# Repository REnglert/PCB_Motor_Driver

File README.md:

# PCB_Motor_Driver

This my designed, printed, soldered, and tested 12V motor driver. 

## Schematic 

## PCB Layout 

## Soldered Board

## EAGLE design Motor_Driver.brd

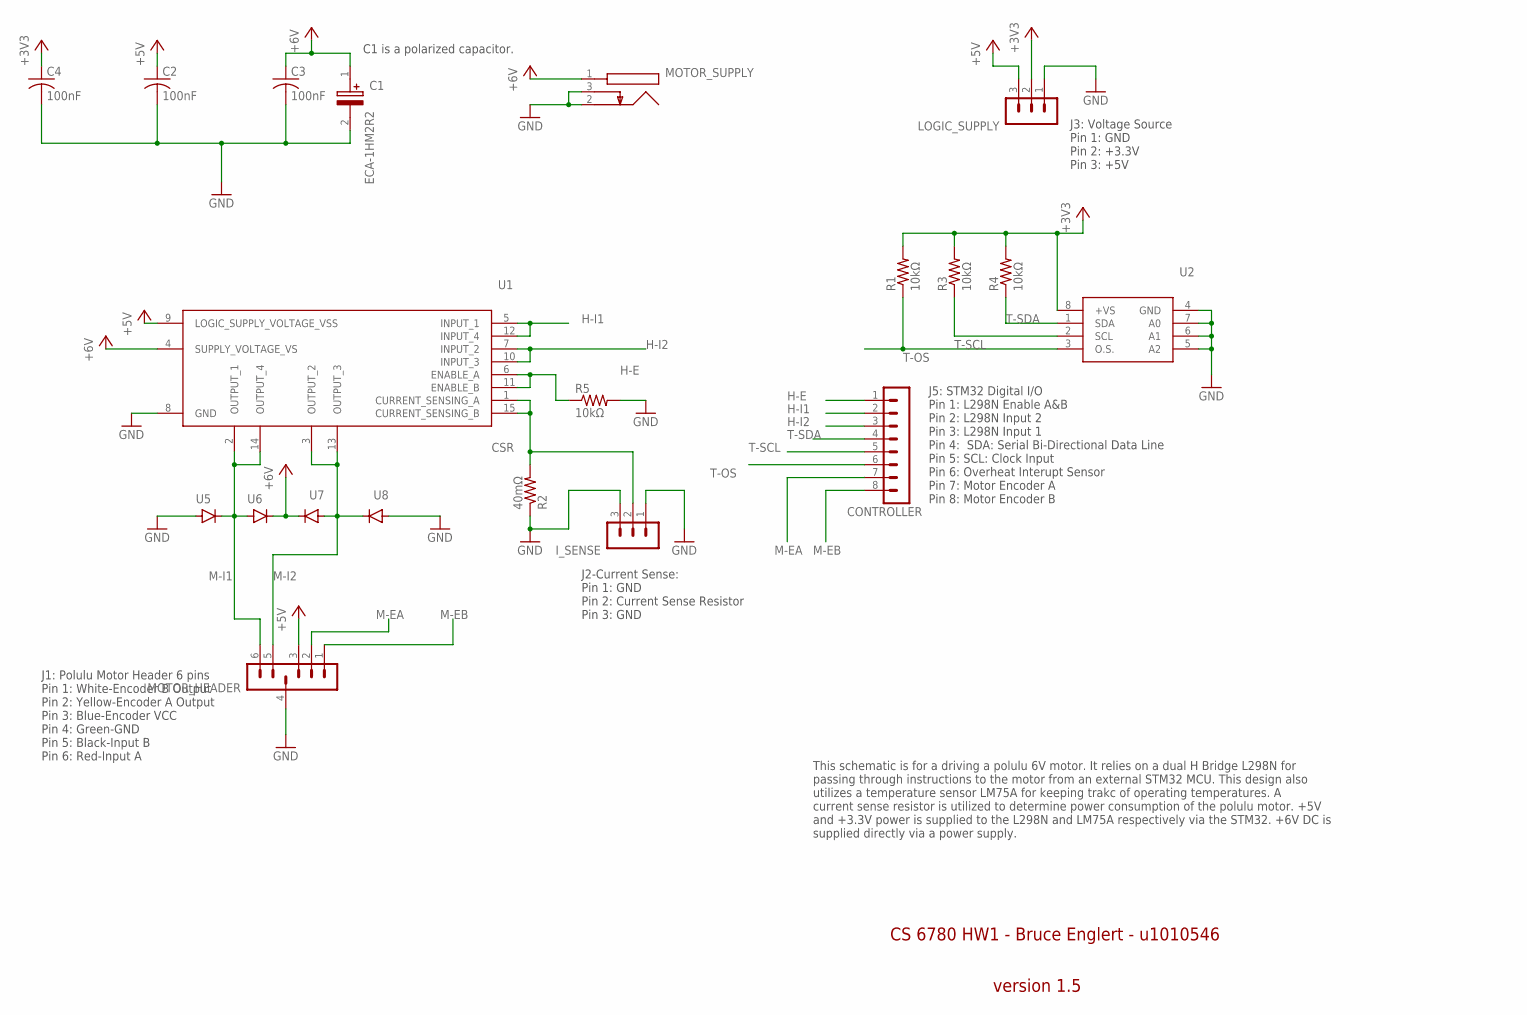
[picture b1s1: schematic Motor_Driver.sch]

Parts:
C1: ECA-1HM2R2; CAPPRD200W55D500H1200
C2, C3, C4: 100nF; C1206
CONTROLLER: MA08-1
I_SENSE: CURRENT_SENSE; MA03-1
LOGIC_SUPPLY: VOLTAGE_SOURCE; MA03-1
MOTOR_HEADER: MA06-1
MOTOR_SUPPLY: SUPPLY_JACK; CONSOCJ2155
R1, R3, R4, R5: 10kΩ; R1206
R2: 40mΩ; R1206
U1: L298N; TO127P500X2020X2210-15P
U2: LM75A; SOIC127P600X175-8N
U5, U6, U7, U8: GF1; SMA-DO214AC

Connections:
+3V3: C4.1, LOGIC_SUPPLY.2, R1.2, R3.2, R4.2, U2.8 (+VS)
+5V: C2.1, LOGIC_SUPPLY.3, MOTOR_HEADER.3, U1.9 (LOGIC_SUPPLY_VOLTAGE_VSS)
+6V: C1.1 (+), C3.1, MOTOR_SUPPLY.1, U1.4 (SUPPLY_VOLTAGE_VS), U6.K (C), U7.K (C)
CSR: I_SENSE.2, R2.2, U1.1 (CURRENT_SENSING_A), U1.15 (CURRENT_SENSING_B)
GND: C1.2 (-), C2.2, C3.2, C4.2, I_SENSE.1, I_SENSE.3, LOGIC_SUPPLY.1, MOTOR_HEADER.4, MOTOR_SUPPLY.2, MOTOR_SUPPLY.3, R2.1, R5.2, U1.8 (GND), U2.4 (GND), U2.5 (A2), U2.6 (A1), U2.7 (A0), U5.A, U8.A
H-E: CONTROLLER.1, R5.1, U1.6 (ENABLE_A), U1.11 (ENABLE_B)
H-I1: CONTROLLER.2, U1.5 (INPUT_1), U1.12 (INPUT_4)
H-I2: CONTROLLER.3, U1.7 (INPUT_2), U1.10 (INPUT_3)
M-EA: CONTROLLER.7, MOTOR_HEADER.2
M-EB: CONTROLLER.8, MOTOR_HEADER.1
M-I1: MOTOR_HEADER.6, U1.2 (OUTPUT_1), U1.14 (OUTPUT_4), U5.K (C), U6.A
M-I2: MOTOR_HEADER.5, U1.3 (OUTPUT_2), U1.13 (OUTPUT_3), U7.A, U8.K (C)
T-OS: CONTROLLER.6, R1.1, U2.3 (O.S.)
T-SCL: CONTROLLER.5, R3.1, U2.2 (SCL)
T-SDA: CONTROLLER.4, R4.1, U2.1 (SDA)

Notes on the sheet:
CS 6780 HW1 - Bruce Englert - u1010546
version 1.5
This schematic is for a driving a polulu 6V motor. It relies on a dual H Bridge L298N for passing through instructions to the motor from an external STM32 MCU. This design also utilizes a temperature sensor LM75A for keeping trakc of operating temperatures. A current sense resistor is utilized to d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
J1: Polulu Motor Header 6 pins Pin 1: White-Encoder B Output Pin 2: Yellow-Encoder A Output Pin 3: Blue-Encoder VCC Pin 4: Green-GND Pin 5: Black-Input B Pin 6: Red-Input A
J2-Current Sense: Pin 1: GND Pin 2: Current Sense Resistor Pin 3: GND
J3: Voltage Source Pin 1: GND Pin 2: +3.3V Pin 3: +5V
J5: STM32 Digital I/O Pin 1: L298N Enable A&B Pin 2: L298N Input 2 Pin 3: L298N Input 1 Pin 4: SDA: Serial Bi-Directional Data Line Pin 5: SCL: Clock Input Pin 6: Overheat Interupt Sensor Pin 7: Motor Encoder A Pin 8: Motor Encoder B
C1 is a polarized capacitor.

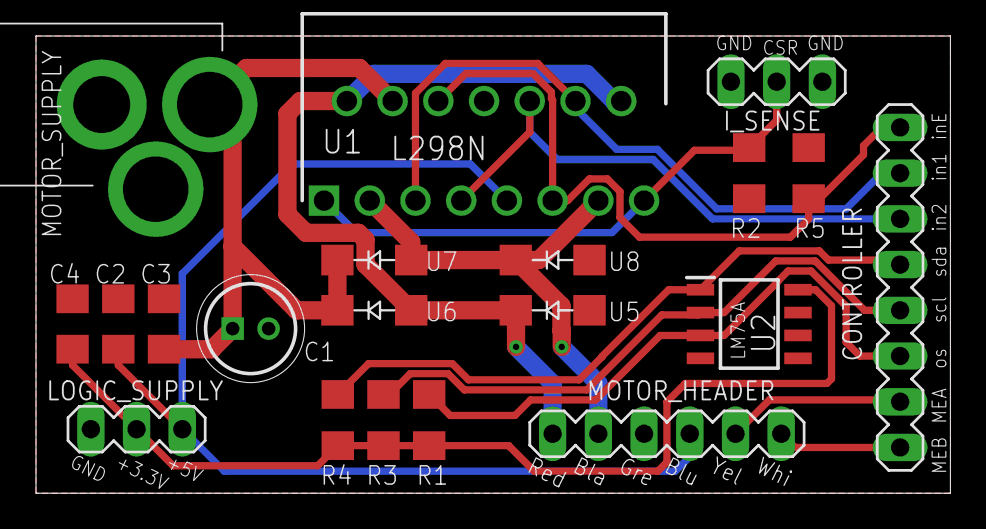
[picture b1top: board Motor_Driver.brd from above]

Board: 2 copper layers, 50.8 x 25.4 mm, 20 parts (0 on the bottom side), 15 nets.

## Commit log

2021-10-06 upload project to public repo
2021-10-06 update schematic image
